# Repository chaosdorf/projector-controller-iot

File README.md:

# moved to Codeberg

This project has been moved to Codeberg: https://codeberg.org/Chaosdorf/projector-controller-iot

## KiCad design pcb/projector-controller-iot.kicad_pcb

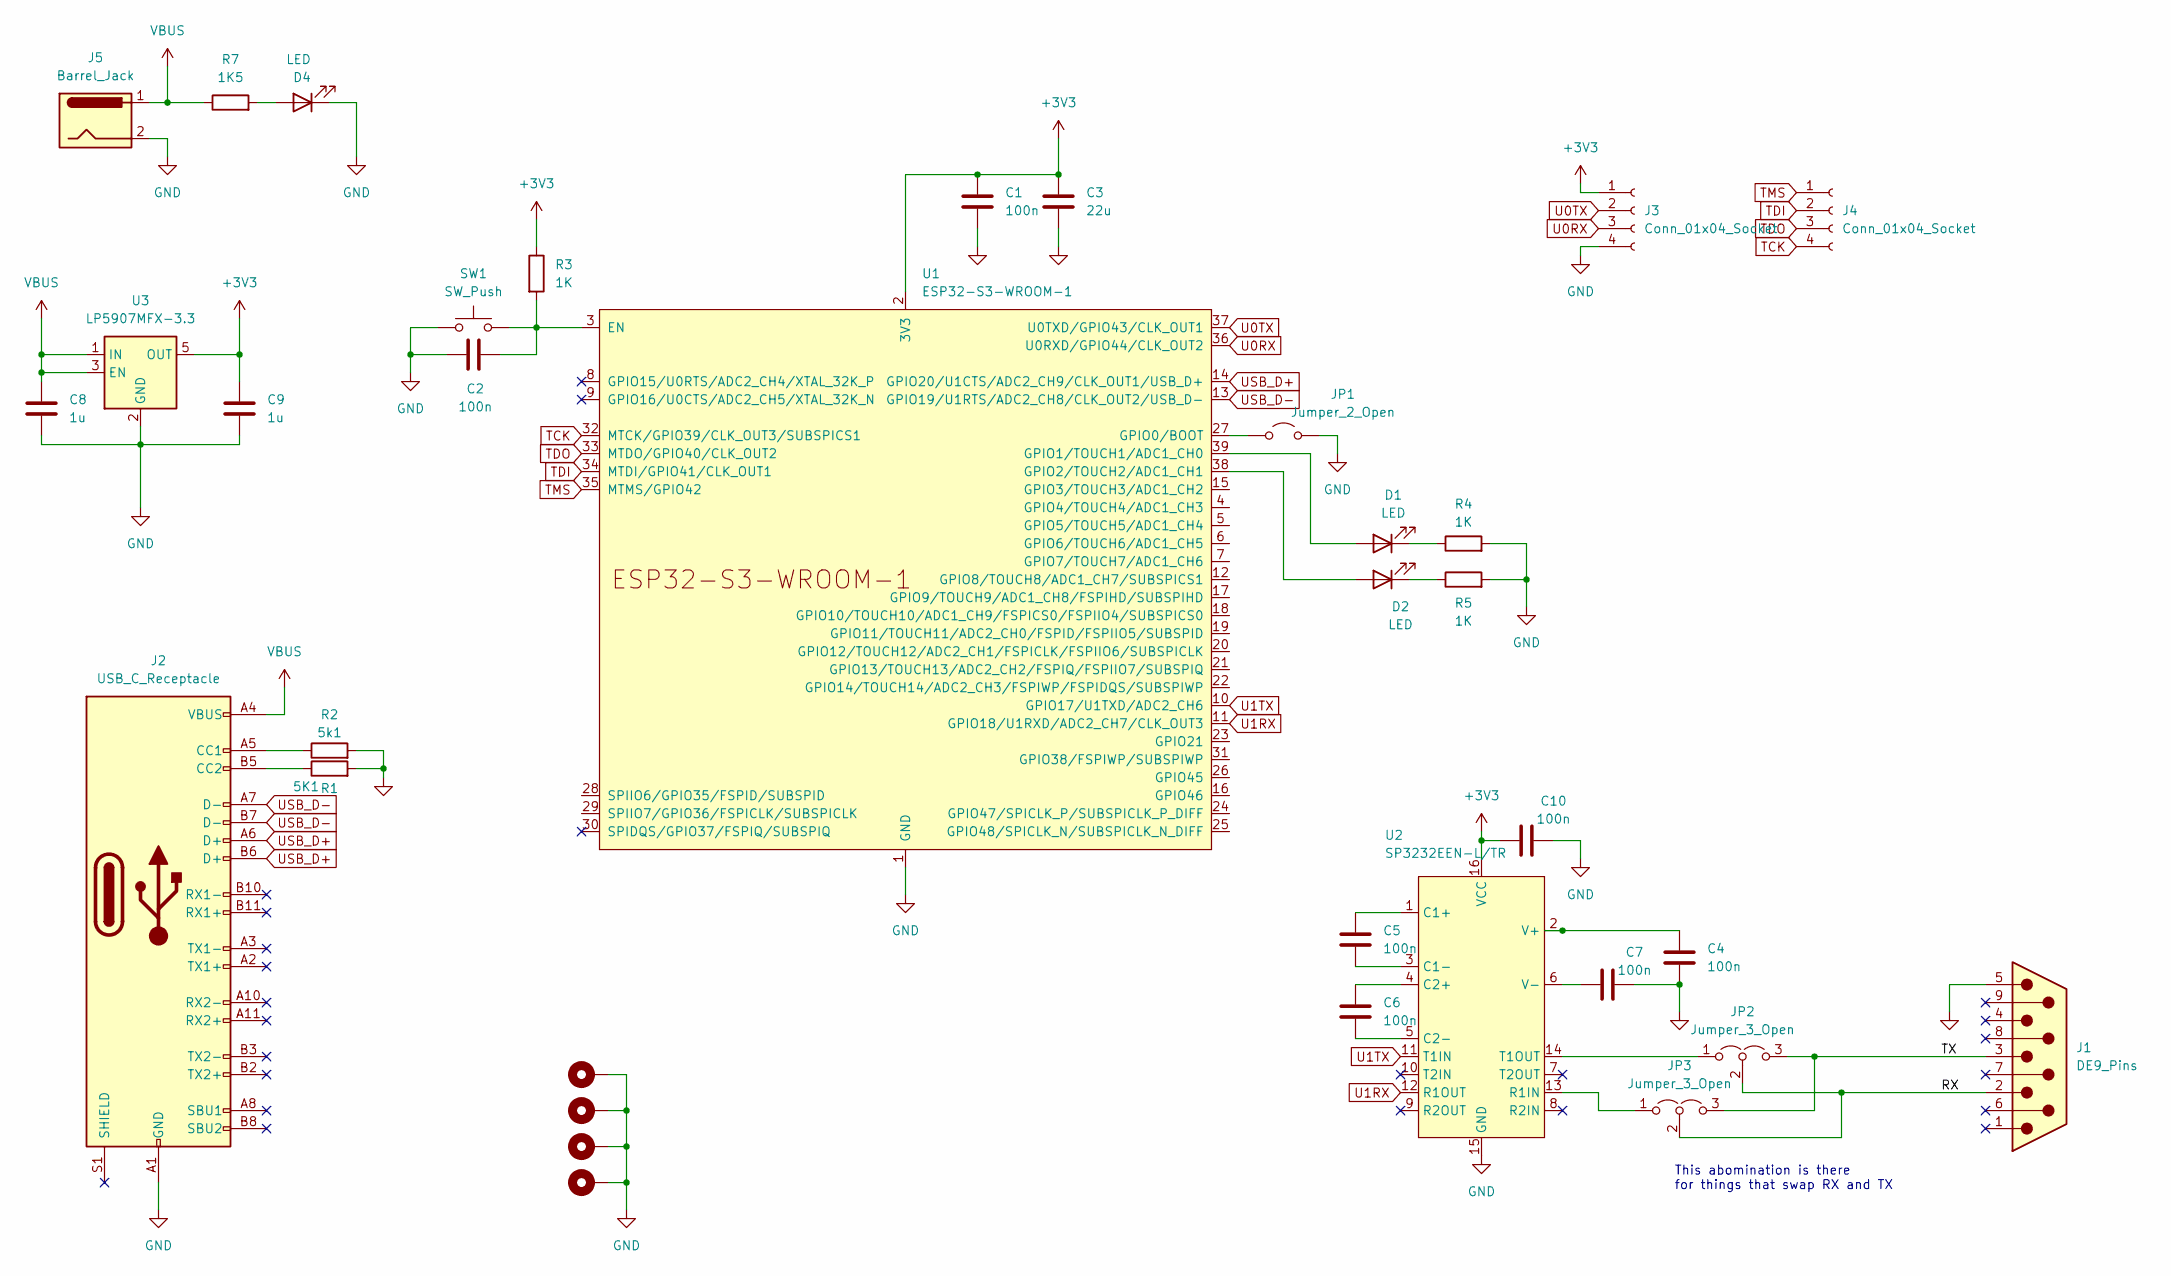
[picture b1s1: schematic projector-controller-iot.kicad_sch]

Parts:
C1, C2, C4, C5, C6, C7, C10: 100n; C_0603_1608Metric_Pad1.08x0.95mm_HandSolder
C3: 22u; C_0603_1608Metric_Pad1.08x0.95mm_HandSolder
C8, C9: 1u; C_0603_1608Metric_Pad1.08x0.95mm_HandSolder
D1, D2, D4: LED; LED_0603_1608Metric_Pad1.05x0.95mm_HandSolder_Triangle
H1, H2, H3, H4: MountingHole_Pad; MountingHole_4.5mm_Pad_Via
J1: DE9_Pins; DB9-TH_LD09P33E4GV00LF
J2: USB_C_Receptacle; USB_C_Receptacle_HRO_TYPE-C-31-M-12
J3, J4: Conn_01x04_Socket; JST_XH_B4B-XH-AM_1x04_P2.50mm_Vertical
J5: Barrel_Jack; DC-IN-TH_DC005
JP1: Jumper_2_Open; PinHeader_1x02_P2.54mm_Vertical
JP2, JP3: Jumper_3_Open
R1: 5K1; R_0603_1608Metric_Pad0.98x0.95mm_HandSolder
R2: 5k1; R_0603_1608Metric_Pad0.98x0.95mm_HandSolder
R3, R4, R5: 1K; R_0603_1608Metric_Pad0.98x0.95mm_HandSolder
R7: 1K5; R_0603_1608Metric_Pad0.98x0.95mm_HandSolder
SW1: SW_Push; SW-SMD_4P-L5.1-W5.1-P3.70-LS6.5-TL_H1.5
U1: ESP32-S3-WROOM-1
U2: SP3232EEN-L/TR; JEITA_SOIC-16_3.9x9.9mm_P1.27mm; LCSC Part C9378
U3: LP5907MFX-3.3; SOT-23-5

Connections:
+3V3: C1.1, C3.1, C9.1, C10.1, J3.1, R3.1, U1.2 (3V3), U2.16 (VCC), U3.5 (OUT)
/RX: J1.2, JP2.2 (C), JP3.1 (A), JP3.2 (C), U2.13 (R1IN)
/TX: J1.3, JP2.1 (A), JP2.3 (B), JP3.3 (B), U2.14 (T1OUT)
GND: C1.2, C2.1, C3.2, C4.2, C7.1, C8.2, C9.2, C10.2, D4.1 (K), H1.1, H2.1, H3.1, H4.1, J1.5, J2.A1 (GND), J2.A12 (GND), J2.B1 (GND), J2.B12 (GND), J3.4, J5.2, JP1.2 (B), R1.2, R2.2, R4.2, R5.2, SW1.1, U1.1 (GND), U1.40 (GND), U1.41 (GND), U2.15 (GND), U3.2 (GND)
unnamed: D1.2 (A), U1.39 (GPIO1/TOUCH1/ADC1_CH0)
unnamed: D1.1 (K), R4.1
unnamed: D2.2 (A), U1.38 (GPIO2/TOUCH2/ADC1_CH1)
unnamed: D2.1 (K), R5.1
unnamed: D4.2 (A), R7.2
unnamed: J2.A5 (CC1), R2.1
unnamed: J2.B5 (CC2), R1.1
unnamed: JP1.1 (A), U1.27 (GPIO0/BOOT)
unnamed: C2.2, R3.2, SW1.2, U1.3 (EN)
unnamed: C5.1, U2.1 (C1+)
unnamed: C5.2, U2.3 (C1-)
unnamed: C6.1, U2.4 (C2+)
unnamed: C6.2, U2.5 (C2-)
unnamed: C4.1, U2.2 (V+)
unnamed: C7.2, U2.6 (V-)
TCK: J4.4, U1.32 (MTCK/GPIO39/CLK_OUT3/SUBSPICS1)
TDI: J4.2, U1.34 (MTDI/GPIO41/CLK_OUT1)
TDO: J4.3, U1.33 (MTDO/GPIO40/CLK_OUT2)
TMS: J4.1, U1.35 (MTMS/GPIO42)
U0RX: J3.3, U1.36 (U0RXD/GPIO44/CLK_OUT2)
U0TX: J3.2, U1.37 (U0TXD/GPIO43/CLK_OUT1)
U1RX: U1.11 (GPIO18/U1RXD/ADC2_CH7/CLK_OUT3), U2.12 (R1OUT)
U1TX: U1.10 (GPIO17/U1TXD/ADC2_CH6), U2.11 (T1IN)
USB_D+: J2.A6 (D+), J2.B6 (D+), U1.14 (GPIO20/U1CTS/ADC2_CH9/CLK_OUT1/USB_D+)
USB_D-: J2.A7 (D-), J2.B7 (D-), U1.13 (GPIO19/U1RTS/ADC2_CH8/CLK_OUT2/USB_D-)
VBUS: C8.1, J2.A4 (VBUS), J2.A9 (VBUS), J2.B4 (VBUS), J2.B9 (VBUS), J5.1, R7.1, U3.1 (IN), U3.3 (EN)

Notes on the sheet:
This abomination is there for things that swap RX and TX

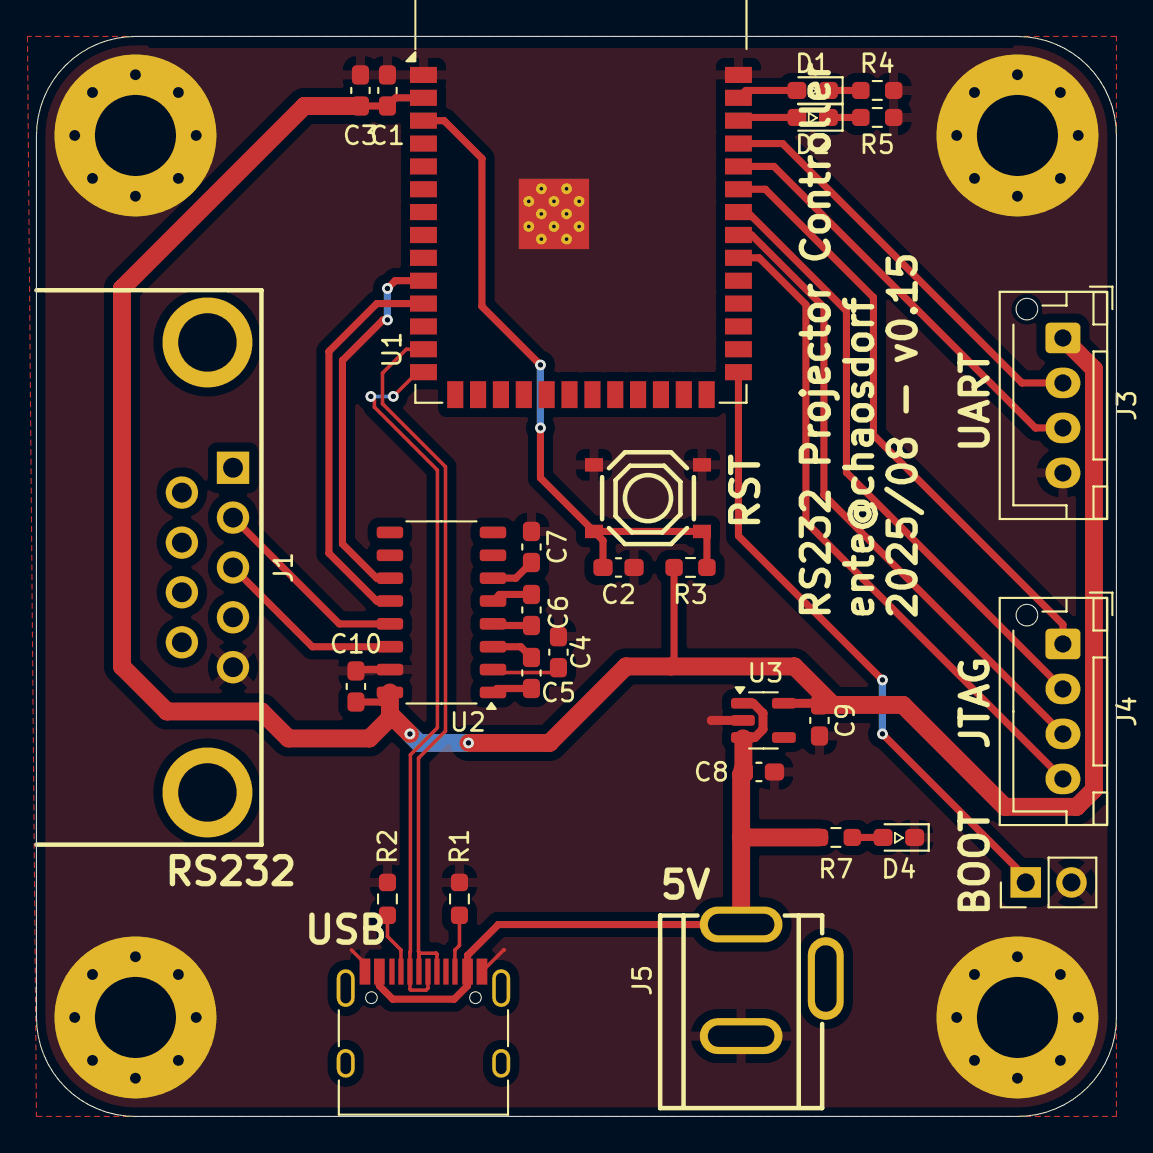
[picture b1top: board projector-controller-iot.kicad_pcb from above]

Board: 2 copper layers, 60.0 x 60.0 mm, 33 parts (0 on the bottom side), 30 nets.

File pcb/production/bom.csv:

Designator,Footprint,Quantity,Value,LCSC Part #
"C1, C10, C2, C4, C5, C6, C7",0603,7,100n,
C3,0603,1,22u,
"C8, C9",0603,2,1u,
"D1, D2, D4",0603,3,LED,
J1,DB9-TH_LD09P33E4GV00LF,1,DE9_Pins,
J2,USB_C_Receptacle_HRO_TYPE-C-31-M-12,1,USB_C_Receptacle,
"J3, J4",JST_XH_B4B-XH-AM_1x04_P2.50mm_Vertical,2,Conn_01x04_Socket,
J5,DC-IN-TH_DC005,1,Barrel_Jack,
JP1,PinHeader_1x02_P2.54mm_Vertical,1,Jumper_2_Open,
"R1, R2",0603,2,5K1,
"R3, R4, R5",0603,3,1K,
R7,0603,1,1K5,
SW1,SW-SMD_4P-L5.1-W5.1-P3.70-LS6.5-TL_H1.5,1,SW_Push,
U1,ESP32-S3-WROOM-1,1,ESP32-S3-WROOM-1,
U2,JEITA_SOIC-16_3.9x9.9mm_P1.27mm,1,SP3232EEN-L/TR,C9378
U3,SOT-23-5,1,LP5907MFX-3.3,

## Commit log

2025-08-29 version where the esp sticks out
2025-08-30 make the esp not stick out
2025-09-03 make fanout make sense
2025-09-08 get it to build
2025-09-08 add gitignore
2025-09-08 esp32c3 gets ip address
2025-09-09 Add renovate.json
2025-09-12 Make MQTT work
2025-09-13 Add projector code
2025-09-13 Bro idk
2025-09-13 use defmt for logging
2025-09-13 Add bracket
2025-09-13 Make MQTT work (?)
2025-09-13 Make home assistant work for power
2025-09-14 Add a bit of ota code
2025-09-14 move ota here
2025-09-14 moved ota code to own branch
2025-09-18 Send initial power state over MQTT
2025-09-22 first working version
2025-09-22 add stuff to gitignore
2026-04-16 moved to Codeberg
